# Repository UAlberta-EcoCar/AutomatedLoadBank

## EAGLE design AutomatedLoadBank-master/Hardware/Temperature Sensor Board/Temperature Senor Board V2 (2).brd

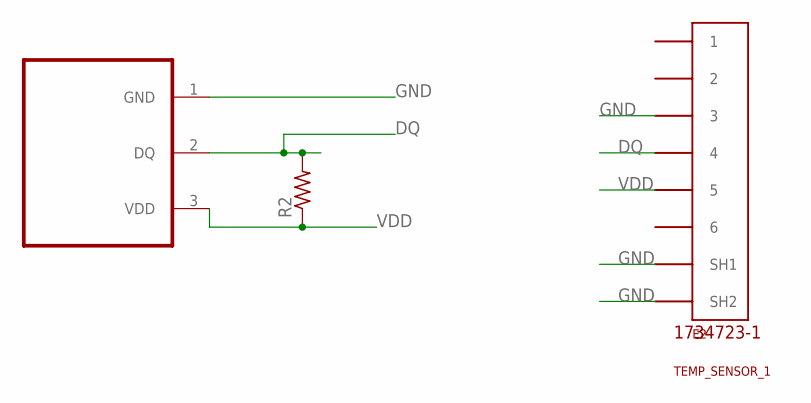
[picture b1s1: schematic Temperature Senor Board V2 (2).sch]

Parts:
E2: TEMP_SENSOR_1; 1734723-1_RJ11
R2: R-US_R0805; R0805
U$1: DS18B; TO92

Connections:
DQ: E2.4, R2.2, U$1.2 (DQ)
GND: E2.3, E2.SH1, E2.SH2, U$1.1 (GND)
VDD: E2.5, R2.1, U$1.3 (VDD)

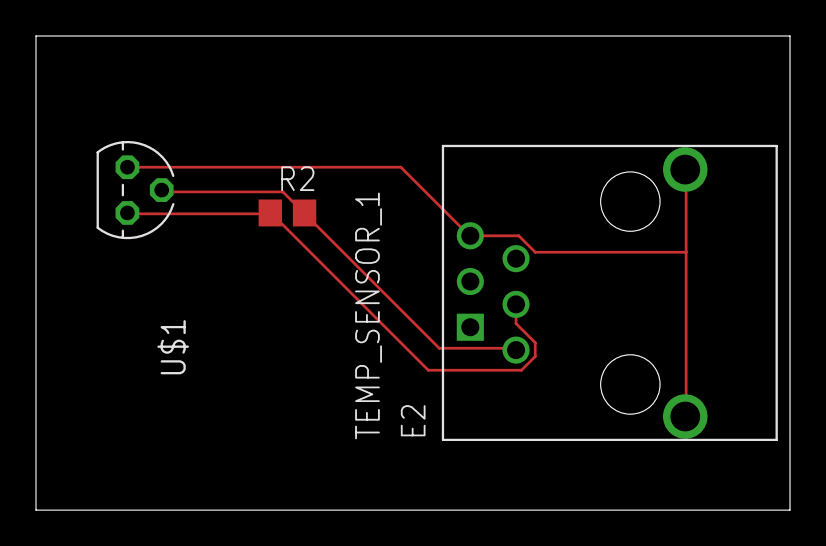
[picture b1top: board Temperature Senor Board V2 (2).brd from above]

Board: 2 copper layers, 41.9 x 26.3 mm, 3 parts (0 on the bottom side), 3 nets.

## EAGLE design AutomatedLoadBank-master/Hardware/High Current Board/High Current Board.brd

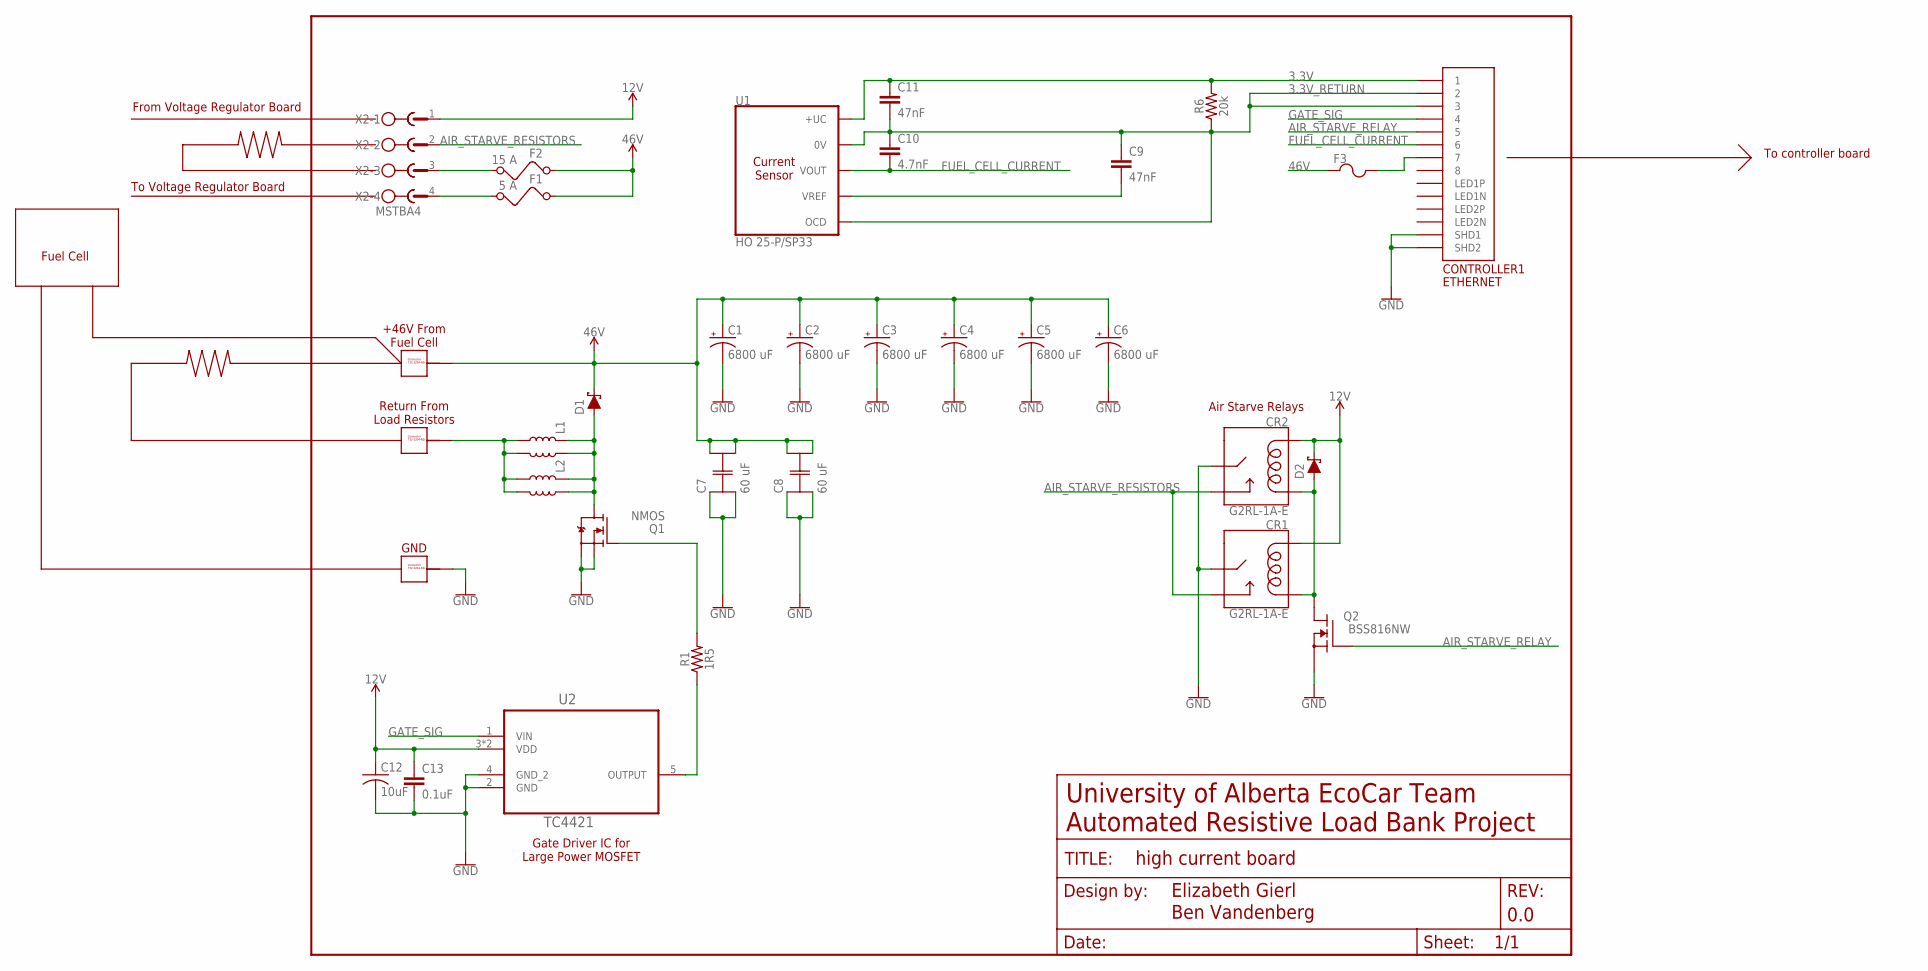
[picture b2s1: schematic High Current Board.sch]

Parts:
C1, C2, C3, C4, C5, C6: 6800 uF; CPOL-RADIAL-10MM-35MM
C7, C8: 60 uF; C4A-0(60)
C9, C11: 47nF; 0805
C10: 4.7nF; 0805
C12: 10uF; C0603
C13: 0.1uF; 0805
CONTROLLER1: ETHERNET; A122645-ND
CR1, CR2: G2RL-1A-E; G2RL-1A-E_RELAY
D1: D-67_HALF-PAK
D2: SOD-123F
F1: 5 A; KEYSTONE_ATM_FUSEHOLDER
F2: 15 A; KEYSTONE_ATM_FUSEHOLDER
F3: POLYFUSE; 1206
FC.GND1, FC.GND2, FC.POS: 732-3204-ND_CONNECTOR; 732-3204-ND
FRAME1: FRAME-LETTERNO_PACKAGE; DUMMY
L1, L2: CMX1616Z171B-10
Q1: NMOS; SOT-227
Q2: BSS816NW; SOT-323
R1: 1R5; SMD_2512
R6: 20k; 0805
U1: HO 25-P/SP33; LEM_HO_25-P
U2: TC4421; TO220-52
X2: MSTBA4

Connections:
3.3V: C11.1, CONTROLLER1.P$1 (1), R6.2, U1.1 (+UC)
3.3V_RETURN: C9.1, C10.1, C11.2, CONTROLLER1.P$2 (2), CONTROLLER1.P$3 (3), R6.1, U1.2 (0V), U1.5 (OCD)
12V: C12.1, C13.1, CR1.1 (COIL1), CR2.1 (COIL1), D2.C, U2.3 (VDD), U2.P$1 (VDD), X2.1
46V: C1.+, C2.+, C3.+, C4.+, C5.+, C6.+, C7.3, C7.4, C8.3, C8.4, D1.C, F1.L1 (1), F1.L2 (1), F2.L1 (1), F2.L2 (1), F3.1, FC.POS.P$1, FC.POS.P$2, FC.POS.P$3, FC.POS.P$4, FC.POS.P$5, FC.POS.P$6, FC.POS.P$7, FC.POS.P$8, FC.POS.P$9, FC.POS.P$10
AIR_STARVE_RELAY: CONTROLLER1.P$5 (5), Q2.1G (G)
AIR_STARVE_RESISTORS: CR1.4 (NO), CR1.5 (NO), CR2.4 (NO), CR2.5 (NO), X2.2
FUEL_CELL_CURRENT: C10.2, CONTROLLER1.P$6 (6), U1.3 (VOUT)
GATE_DRIVE: Q1.G, Q1.G2 (G), R1.P$2 (2)
GATE_SIG: CONTROLLER1.P$4 (4), U2.1 (VIN)
GND: C1.-, C2.-, C3.-, C4.-, C5.-, C6.-, C7.1, C7.2, C8.1, C8.2, C12.2, C13.2, CONTROLLER1.P$13 (SHD1), CONTROLLER1.P$14 (SHD2), CR1.3 (MAIN), CR1.6 (MAIN), CR2.3 (MAIN), CR2.6 (MAIN), FC.GND2.P$1, FC.GND2.P$2, FC.GND2.P$3, FC.GND2.P$4, FC.GND2.P$5, FC.GND2.P$6, FC.GND2.P$7, FC.GND2.P$8, FC.GND2.P$9, FC.GND2.P$10, Q1.S1 (S), Q1.S2 (S1), Q1.S3 (S), Q1.S4 (S1), Q2.2S (S), U2.2 (GND), U2.4 (GND_2)
unnamed: C9.2, U1.4 (VREF)
unnamed: FC.GND1.P$1, FC.GND1.P$2, FC.GND1.P$3, FC.GND1.P$4, FC.GND1.P$5, FC.GND1.P$6, FC.GND1.P$7, FC.GND1.P$8, FC.GND1.P$9, FC.GND1.P$10, L1.R1 (B1), L1.R2 (B2), L1.R11 (B1), L1.R22 (B2), L2.R1 (B1), L2.R2 (B2), L2.R11 (B1), L2.R22 (B2)
unnamed: CR1.8 (COIL2), CR2.8 (COIL2), D2.A, Q2.3D (D)
unnamed: L1.L1 (T1), L1.L2 (T2), L1.L11 (T1), L1.L22 (T2), L2.L1 (T1), L2.L2 (T2), L2.L11 (T1), L2.L22 (T2), Q1.D, Q1.D2 (D)
unnamed: F2.R1 (2), F2.R2 (2), X2.3
unnamed: F1.R1 (2), F1.R2 (2), X2.4
unnamed: R1.P$1 (1), U2.5 (OUTPUT)
unnamed: CONTROLLER1.P$7 (7), F3.2

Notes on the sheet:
University of Alberta EcoCar Team Automated Resistive Load Bank Project
Elizabeth Gierl
Current Sensor
+46V From Fuel Cell
Return From Load Resistors
GND
Air Starve Relays
Gate Driver IC for Large Power MOSFET
Fuel Cell
To controller board
To Voltage Regulator Board
From Voltage Regulator Board

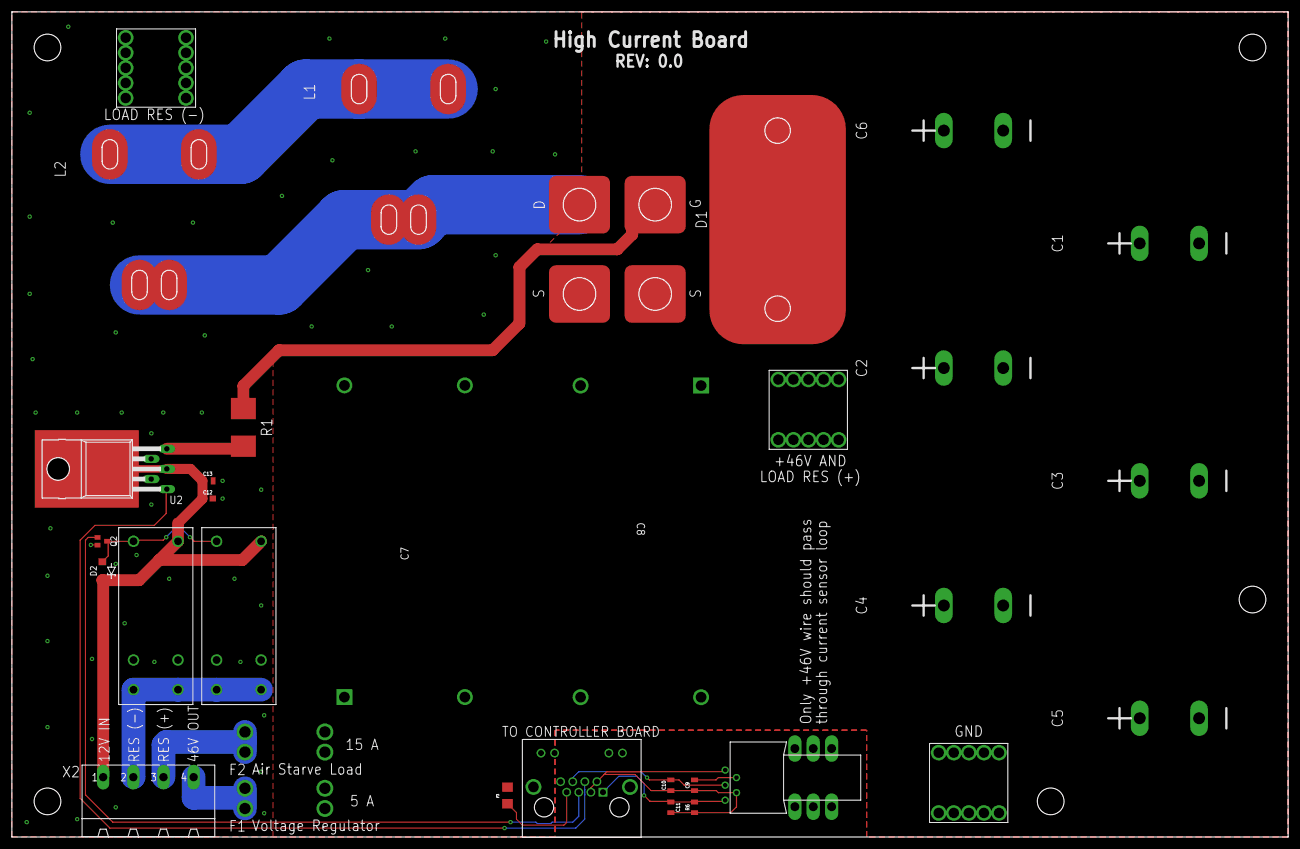
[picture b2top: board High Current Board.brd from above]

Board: 2 copper layers, 215.0 x 139.0 mm, 34 parts (0 on the bottom side), 18 nets.

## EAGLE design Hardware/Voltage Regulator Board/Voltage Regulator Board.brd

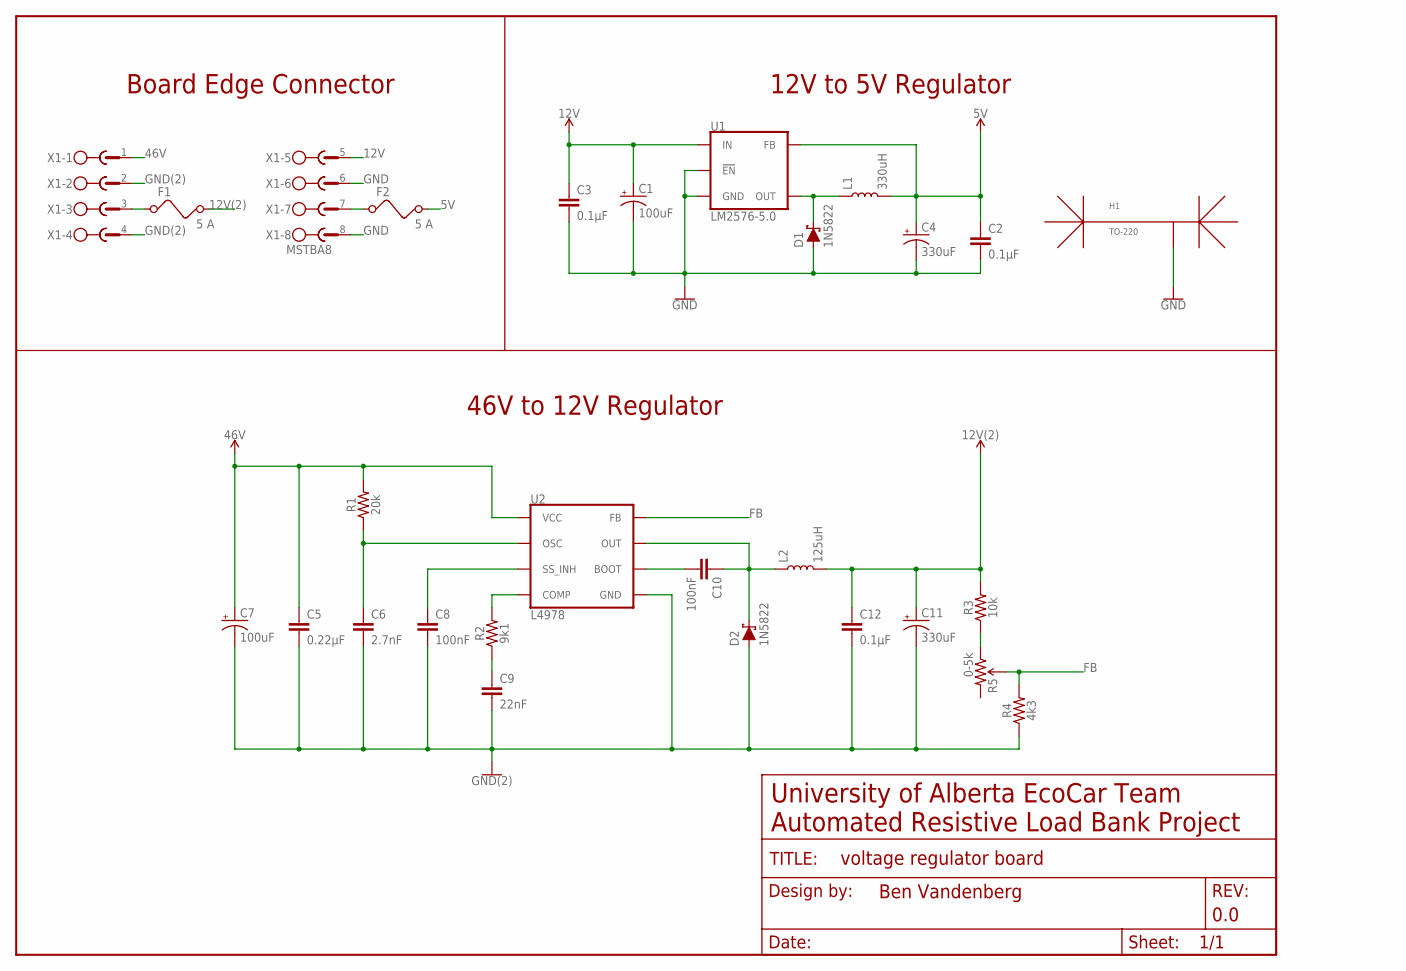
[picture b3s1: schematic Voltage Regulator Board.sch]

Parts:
C1, C7: 100uF; CPOL-RADIAL-3.5MM-8MM
C2, C3, C12: 0.1µF; 0805
C4, C11: 330uF; CPOL-RADIAL-5MM-10MM
C5: 0.22µF; 0805
C6: 2.7nF; 0805
C8, C10: 100nF; 0805
C9: 22nF; 0805
D1, D2: 1N5822; DO201T15
F1, F2: 5 A; KEYSTONE_ATM_FUSEHOLDER
FRAME1: FRAME-LETTERNO_PACKAGE; DUMMY
H1: TO-220; HSE-B250-04H_HEATSINK
L1: 330uH; 330UH_PTH_INDUCTOR
L2: 125uH; 125UH_PTH_INDUCTOR
R1: 20k; 0805
R2: 9k1; 0805
R3: 10k; 0805
R4: 4k3; 0805
R5: 0-5k; TRIM_POT
U1: LM2576-5.0; TO220-5
U2: L4978; DIP08
X1: MSTBA8

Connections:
5V: C2.1, C4.+, F2.R1 (2), F2.R2 (2), L1.P$2 (2), U1.4 (FB)
12V: C1.+, C3.1, U1.1 (IN), X1.5
12V(2): C11.+, C12.1, F1.R1 (2), F1.R2 (2), L2.P$2 (2), R3.2
46V: C5.1, C7.+, R1.2, U2.5 (VCC), X1.1
FB: R4.2, R5.2 (WIPER), U2.8 (FB)
GND: C1.-, C2.2, C3.2, C4.-, D1.A, H1.GND@1, H1.GND@2, U1.3 (GND), U1.5 (!EN), X1.6, X1.8
GND(2): C5.2, C6.2, C7.-, C8.2, C9.2, C11.-, C12.2, D2.A, R4.1, U2.1 (GND), X1.2, X1.4
unnamed: F1.L1 (1), F1.L2 (1), X1.3
unnamed: C6.1, R1.1, U2.3 (OSC)
unnamed: C8.1, U2.2 (SS_INH)
unnamed: R2.2, U2.7 (COMP)
unnamed: C9.1, R2.1
unnamed: F2.L1 (1), F2.L2 (1), X1.7
unnamed: C10.2, U2.6 (BOOT)
unnamed: C10.1, D2.C, L2.P$1 (1), U2.4 (OUT)
unnamed: R3.1, R5.1 (CCW)
OUT: D1.C, L1.P$1 (1), U1.2 (OUT)

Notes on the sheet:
University of Alberta EcoCar Team Automated Resistive Load Bank Project
12V to 5V Regulator
46V to 12V Regulator
Board Edge Connector

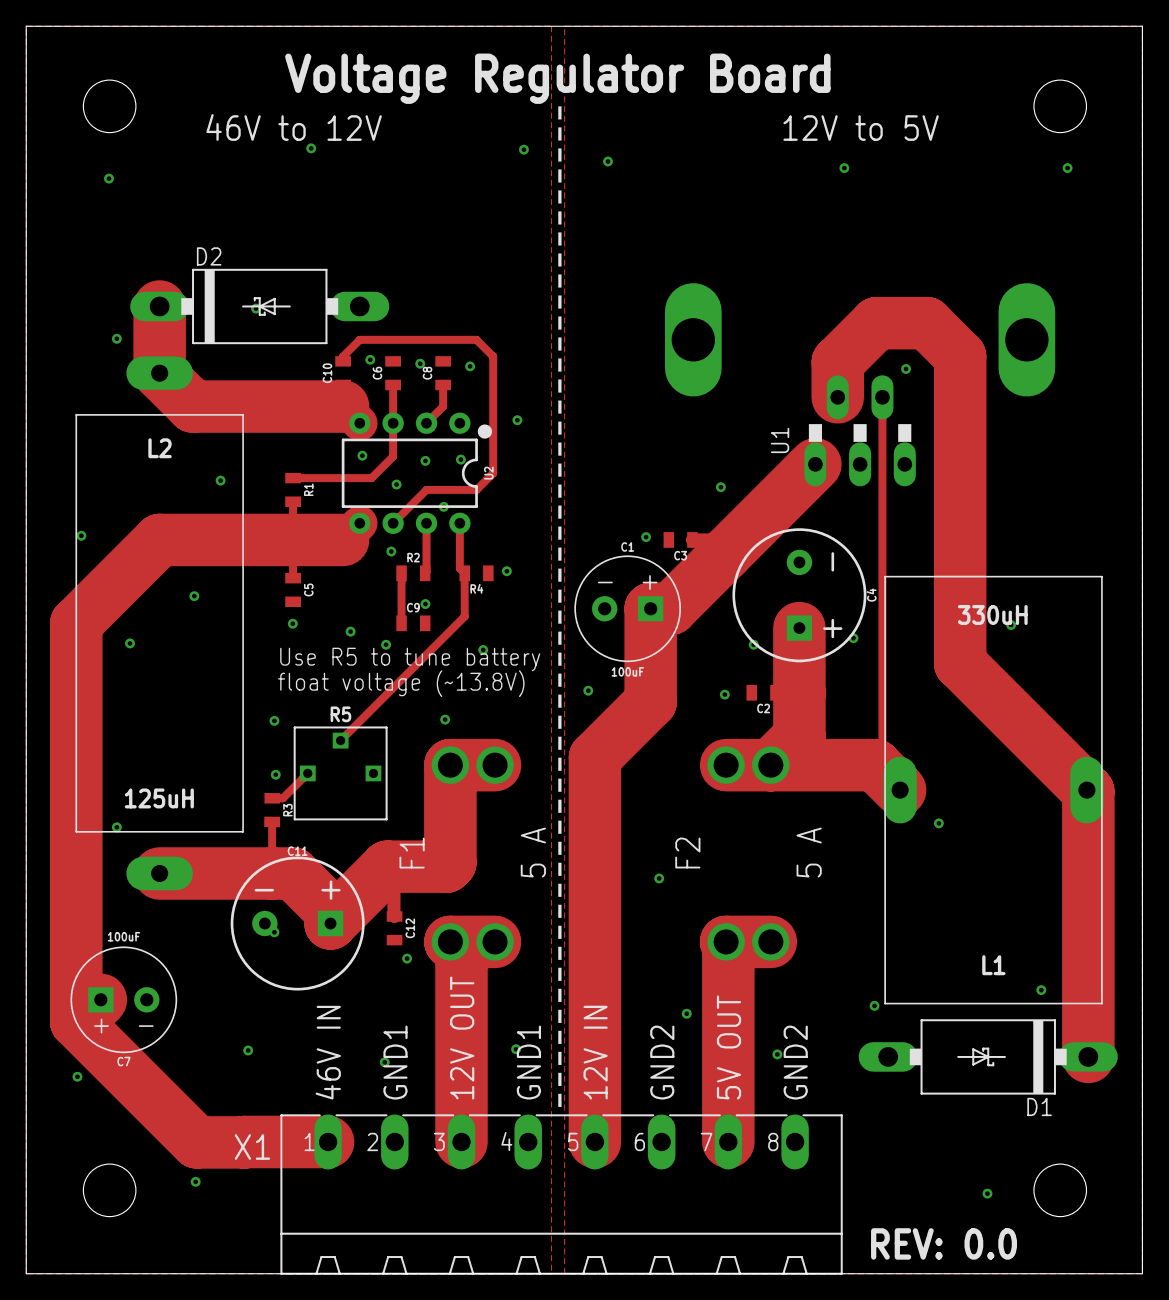
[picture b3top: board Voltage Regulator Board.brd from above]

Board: 2 copper layers, 85.0 x 95.0 mm, 28 parts (0 on the bottom side), 17 nets.

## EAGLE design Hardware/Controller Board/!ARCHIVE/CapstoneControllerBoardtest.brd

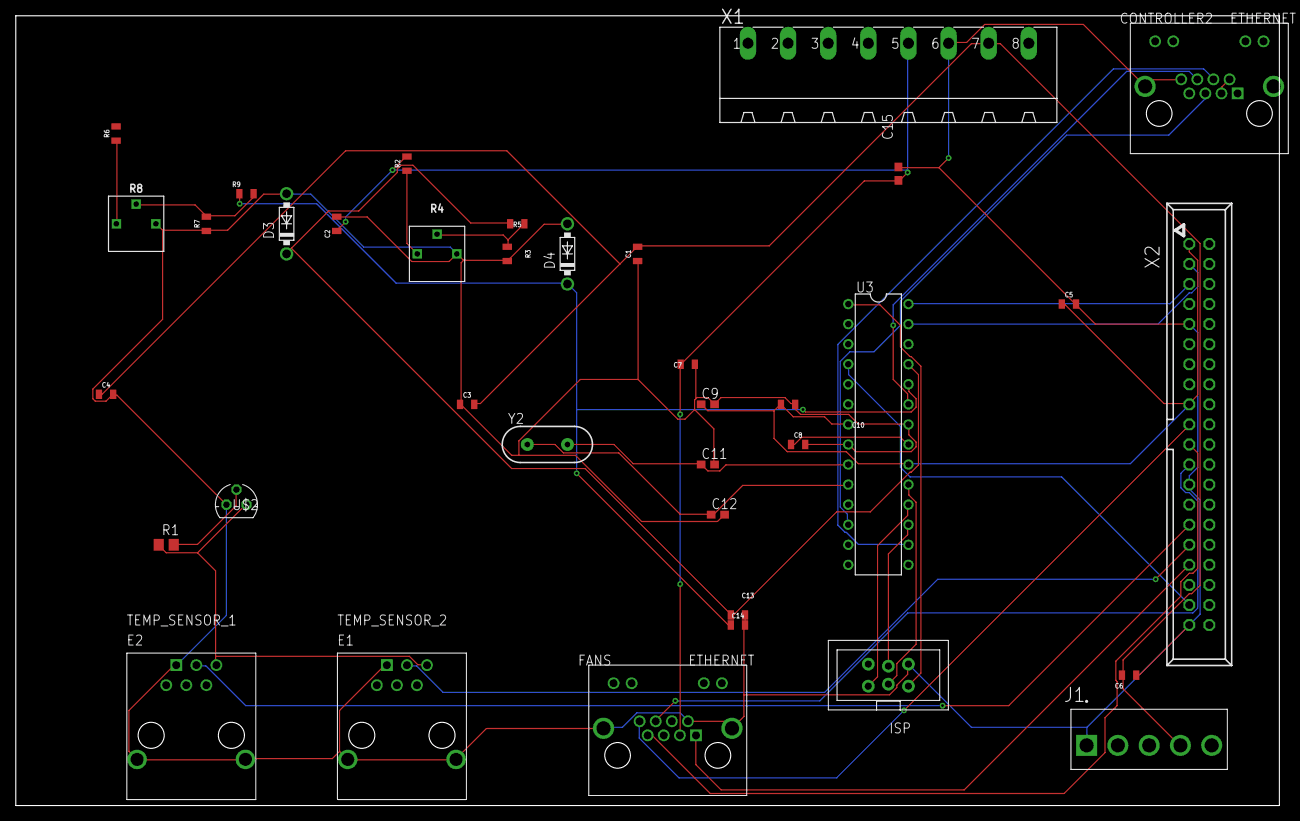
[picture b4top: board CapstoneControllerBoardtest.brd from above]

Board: 2 copper layers, 160.0 x 100.0 mm, 38 parts (0 on the bottom side), 32 nets.

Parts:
C1, C2, C3, C4, C5, C6, C7, C8, C10, C13, C14: 0.1uF; 0805
C9, C15: 10uF; C0603
C11, C12: 22pF; C0603
CONTROLLER2: ETHERNET; A122645-ND
D3, D4: 3.3V Zener; DO41-7.6
E1: TEMP_SENSOR_2; 1734723-1_RJ11
E2: TEMP_SENSOR_1; 1734723-1_RJ11
FANS: ETHERNET; A122645-ND
FRAME2: FRAME-LETTERNO_PACKAGE; DUMMY
ISP: AVRISP-BOX
J1: 3-641208-5; TE_3-641208-5
R1: R0805
R2: 2.4k; 0805
R3: 1.2k; 0805
R4, R8: 0-5k; TRIM_POT
R5, R9: 5k; 0805
R6: 16k; 0805
R7: 1.3k; 0805
U3: ATmega328P PDIP; PDIP-T28
U$2: DS18B; TO92
X1: MSTBA8
X2: 057-040-1
Y2: HC49US

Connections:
3.3V: C5.1, C9.1, C10.1, U3.7, U3.20, X2.1, X2.17
3.3V_RETURN: CONTROLLER2.P$2, CONTROLLER2.P$3
12V: C2.1, C7.1, C15.1, FANS.P$3, R2.2, X1.5
+5V: C1.2, C3.2, C4.1, C6.1, J1.4, X1.7
AIR_STARVE_RELAY: CONTROLLER2.P$5, U3.12
DQ_1: E2.2, X2.29
DQ_2: E1.2, X2.31
DQ_3: R1.2, U$2.2
EXTRA_PIN_1: FANS.P$8, X2.19
EXTRA_PIN_2: FANS.P$7, X2.21
EXTRA_PIN_3: FANS.P$6, X2.23
FAN_PWM: FANS.P$1, X2.33
FUEL_CELL_CURRENT1: CONTROLLER2.P$6, U3.23
GATE_DRIVE: CONTROLLER2.P$4, U3.16
GND: C1.1, C2.2, C3.1, C4.2, C5.2, C6.2, C7.2, C8.2, C9.2, C10.2, C11.2, C12.2, C13.2, C14.2, C15.2, CONTROLLER2.P$8, CONTROLLER2.P$13, CONTROLLER2.P$14, D3.A, D4.A, E1.1, E1.SH1, E1.SH2, E2.1, E2.SH1, E2.SH2, FANS.P$2, FANS.P$13, FANS.P$14, ISP.6, J1.1, R3.1, R4.3, R7.1, R8.3, U3.8, U3.22, U$2.1, X1.6, X2.9, X2.25, X2.39
LOAD_ENABLE: U3.4, X2.37
unnamed: C8.1, U3.21
unnamed: ISP.1, U3.18
unnamed: ISP.3, U3.19
unnamed: R2.1, R4.1
unnamed: R6.1, R8.1
unnamed: R3.2, R4.2, R5.2
unnamed: ISP.4, U3.17
unnamed: C11.1, U3.9, Y2.2
unnamed: C12.1, U3.10, Y2.1
unnamed: R7.2, R8.2, R9.2
RESET: ISP.5, U3.1
SCALED_BATT_V: C13.1, D3.C, R5.1, U3.25
SCALED_FUEL_CELL_V: C14.1, D4.C, R9.1, U3.24
SCL: U3.28, X2.5
SDA: U3.27, X2.3
VDD: E1.3, E2.3, R1.1, U$2.3

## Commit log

2019-11-16 removed duplicate files :^)
2019-11-16 test changes were made to learn git
2020-03-14 Updated GUI Directory
2023-11-25 no changes
2023-12-02 editing
2023-12-02 to92-package
2023-12-02 work on temp sensor board
2023-12-02 Changed Schematic for Temp Sens Board
2023-12-02 Gerber File Changed
2023-12-03 Added File for Temperature Sensor Board 1 and Temperature Sensor Board 2
2023-12-28 random push
2023-12-29 some change s
2024-01-01 edit
2024-01-01 complete gerber for temp sensors
2024-01-04 proj create
2024-01-04 sch capture
2024-01-04 sch capture 2
2024-01-05 started new schematicccccccc:)))))))
2024-01-06 final edit
2024-01-06 Updated Schematic
2024-01-07 PCB Update for the schematic
2024-01-07 final update
2024-01-07 PCB Updated
2024-01-11 PCB Update - HC
2024-01-11 PCB Update 1.0
    Needs a Revision Check and we good
2024-01-11 Text update

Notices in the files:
parts and their libraries:
SparkFun-Aesthetics: Licensing: Creative Commons ShareAlike 4.0 International - https://creativecommons.org/licenses/by-sa/4.0
SparkFun-Aesthetics: Released under the Creative Commons Attribution Share-Alike 4.0 License
SparkFun-Aesthetics: https://creativecommons.org/licenses/by-sa/4.0
